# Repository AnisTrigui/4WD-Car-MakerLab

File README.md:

# 4WD Car MakerLab
 4 Wheeld Drive Car controlled by a Mobile App through Bluetooth

Overview
--------
Smart Arduino Car:
+ Autonomous mode using Ultrasonic sensor for obstacle avoidance
+ Remote control through Bluetooth with Android smart phone
+ Camera to send photos to Android phone over Bluetooth

Materials
--------
+ Arduino Uno
+ 7V - 12V Battery Holder with batteries
+ Multiple Male/Female to Male/Female jumper wires
+ Ultrasonic Module HC-SR04
+ DC 3v 5V 6V 4WD Smart Robot Car Chassis Kits (or Equivalent)
+ Serial 6 Pin Bluetooth Module HC-05
+ Motor Drive Controller Module L298N
+ Android Smartphone with Bluetooth
+ SainSmart Digital Analog Module V5 Sensor Shield (or Equivalent shield with multiple VCC, GND)
+ Miniature TTL Serial JPEG Camera with NTSC Video

Mobile App Bluetooth Controller Link
--------
https://play.google.com/store/apps/details?id=braulio.calle.bluetoothRCcontroller&hl=fr&gl=US

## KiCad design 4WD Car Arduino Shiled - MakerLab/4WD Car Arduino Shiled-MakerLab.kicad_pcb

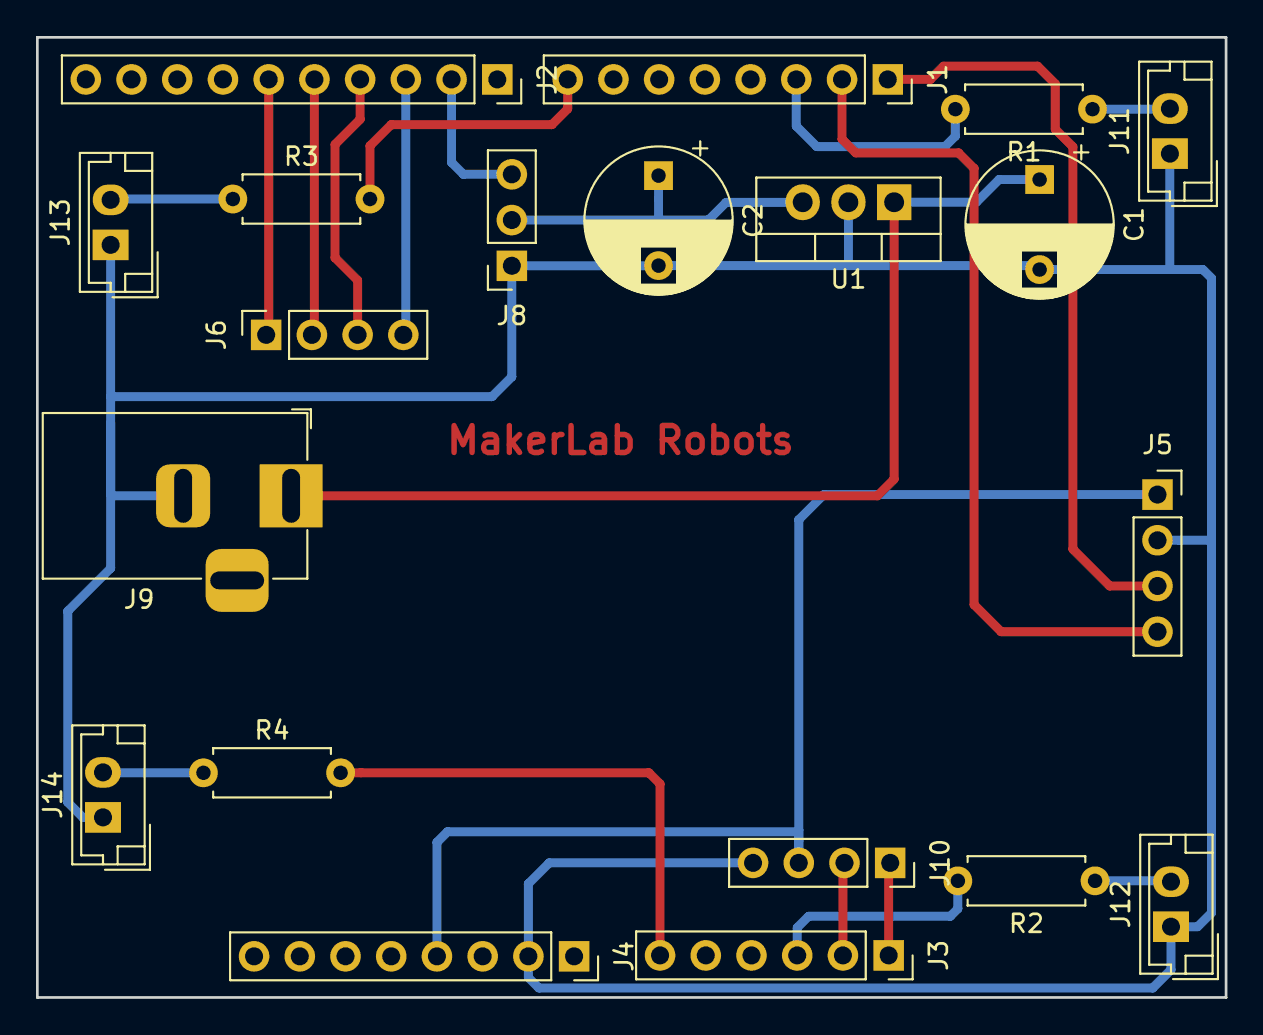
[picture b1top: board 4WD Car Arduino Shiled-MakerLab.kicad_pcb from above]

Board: 2 copper layers, 66.0 x 53.3 mm, 20 parts (0 on the bottom side), 21 nets.

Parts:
C1, C2: 10uF; CP_Radial_D8.0mm_P5.00mm
J1, J4: Conn_01x08_Male; PinSocket_1x08_P2.54mm_Vertical
J2: Conn_01x10_Male; PinSocket_1x10_P2.54mm_Vertical
J3: Conn_01x06_Male; PinSocket_1x06_P2.54mm_Vertical
J5, J6, J10: Conn_01x04_Female; PinSocket_1x04_P2.54mm_Vertical
J8: Conn_01x03_Female; PinSocket_1x03_P2.54mm_Vertical
J9: Conn_01x02_Male; BarrelJack_Horizontal
J11, J12, J13, J14: Conn_01x02_Male; JST_EH_B02B-EH-A_1x02_P2.50mm_Vertical
R1, R2, R3, R4: 220ohm; R_Axial_DIN0207_L6.3mm_D2.5mm_P7.62mm_Horizontal
U1: L7806; TO-220-3_Vertical

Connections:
5V: J4.4, J5.1, J10.3
+6V: C2.1, J8.2, U1.3
+12V: C1.1, J9.1, U1.1
GND: C1.2, C2.2, J4.2, J5.2, J8.1, J9.2, J10.4, J11.1, J12.1, J13.1, J14.1, U1.2
IN1: J2.3, J6.4
IN2: J2.4, J6.3
IN3: J2.5, J6.2
IN4: J2.6, J6.1
unnamed: J11.2, R1.1
unnamed: J12.2, R2.1
unnamed: J13.2, R3.1
unnamed: J14.2, R4.1
RX: J1.2, J5.4
SCL: J3.1, J10.1
SDA: J3.2, J10.2
TX: J1.1, J5.3
led1: J1.3, R1.2
led2: J3.3, R2.2
led3: J1.8, R3.2
led4: J3.6, R4.2
servo: J2.2, J8.3

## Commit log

2021-10-02 Project init
2021-10-02 MAL1
